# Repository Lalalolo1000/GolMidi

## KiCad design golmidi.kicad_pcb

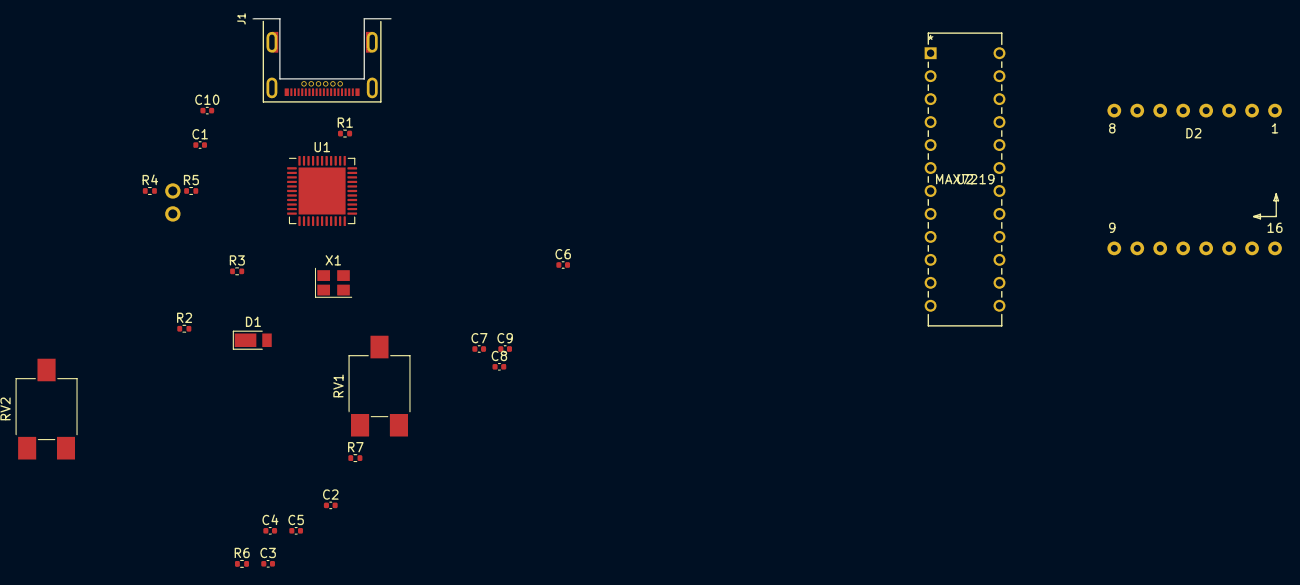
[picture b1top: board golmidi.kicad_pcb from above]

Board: 2 copper layers, 26 parts (0 on the bottom side), 36 nets, no tracks yet.

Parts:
C1, C2, C3, C4, C5, C10: 0u1; C_0402_1005Metric
C6: 4u7; C_0402_1005Metric
C7, C8: 22p; C_0402_1005Metric
C9: 1u; C_0402_1005Metric
D1: D_Schottky; D_PowerDI-123
D2: DISP_LED_MAT_8x8_COM_ANODE; LED_8x8_1.9MM_20x20MM_Horiz
J1: USB-C; CX70M-24P1
J2: 01x02; Pins2
R1, R2: 5k1; R_0402_1005Metric
R3, R6: 10k; R_0402_1005Metric
R4, R5: 22; R_0402_1005Metric
R7: R; R_0402_1005Metric
RV1, RV2: R_POT; Potentiometer_ACP_CA6-VSMD_Vertical
U1: ATmega32U4; QFN-44-1EP_7x7mm_P0.5mm_EP5.2x5.2mm
U2: MAX7219; MAX7219CNG&plus_
X1: 16MHz; Crystal_SMD_SeikoEpson_FA238-4Pin_3.2x2.5mm

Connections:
/D+: J1.A6, J1.B6, J2.1, R4.2
/D-: J1.A7, J1.B7, J2.2, R5.2
/PB1: U1.9, U2.13
/PB6: U1.30, U2.12
/PB7: U1.12, U2.1
/PF6: RV1.2, U1.37
/PF7: RV2.2, U1.36
/RESET: R3.1, U1.13
GND: C1.2, C2.2, C3.2, C4.2, C5.2, C6.2, C7.2, C8.2, C9.2, C10.2, J1.A1, J1.A12, J1.B1, J1.B12, J1.S1, R1.1, R2.1, R6.1, RV1.3, RV2.3, U1.5, U1.15, U1.23, U1.33, U1.35, U1.43, U1.45, U2.4, U2.9, X1.2, X1.4
unnamed: C7.1, U1.17, X1.1
unnamed: C8.1, U1.16, X1.3
unnamed: C9.1, U1.6
unnamed: C10.1, U1.42
unnamed: D2.1, U2.23
unnamed: D2.2, U2.15
unnamed: D2.3, U2.11
unnamed: D2.4, U2.6
unnamed: D2.5, U2.17
unnamed: D2.6, U2.3
unnamed: D2.7, U2.21
unnamed: D2.8, U2.16
unnamed: D2.9, U2.22
unnamed: D2.10, U2.7
unnamed: D2.11, U2.10
unnamed: D2.12, U2.20
unnamed: D2.13, U2.2
unnamed: D2.14, U2.14
unnamed: D2.15, U2.5
unnamed: D2.16, U2.8
unnamed: J1.A5, R1.2
unnamed: J1.B5, R2.2
unnamed: R4.1, U1.4
unnamed: R5.1, U1.3
unnamed: R7.2, U2.18
VBUS: C5.1, C6.1, D1.2, J1.A4, J1.A9, J1.B4, J1.B9, R6.2, U1.2, U1.7
VCC: C1.1, C2.1, C3.1, C4.1, D1.1, R3.2, R7.1, RV1.1, RV2.1, U1.14, U1.24, U1.34, U1.44, U2.19

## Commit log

2021-01-13 fixed 8x8 Led Matrix footprint
2021-01-15 fixed overlapping traces
2021-01-18 Started to clean pcb-layout

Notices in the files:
parts and their libraries:
Copyright 2016 Accelerated Designs. All rights reserved.
